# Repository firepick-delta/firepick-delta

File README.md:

### FirePick Delta Hardware/Mechanical Repo

#### Summary / Context

Design and Manufacturing Specifications for [FirePick Delta](http://delta.firepick.org).  If you're a developer wanting to help, the best way to do that is to join the [mailing list](https://groups.google.com/forum/#!forum/firepick) and start a line of communication there.  

This repo only contains the hardware (sch/pcb) and mechanical (3d) files for FirePick Delta.  It inherits software from OpenPnP, Marlin, and FirePick.  Other repo's of interest for FirePick Delta:

* https://github.com/firepick-delta/openpnp
* https://github.com/firepick-delta/Marlin
* https://github.com/firepick1/FireREST
* https://github.com/firepick1/FireBOM

#### Mechanical Assembly Parts Tree, Instructions, and BOM

Please click the link below to navigate the mechanical assembly with our FireBOM wiki documentation system:

[AFPD0001](AFPD0001) FirePick Delta Hacker-Developer Edition

#### Licensing

These files are licensed under [*Creative Commons Attribution-ShareAlike (CC BY-SA)*](https://creativecommons.org/licenses/by-sa/4.0/legalcode).  Commercial use is OK, but you are required under the license conditions to share your changes with the internet, and also credit the FirePick Delta team.

This license lets others remix, tweak, and build upon your work even for commercial purposes, as long as they credit you and license their new creations under the identical terms. This license is often compared to “copyleft” free and open source software licenses. All new works based on yours will carry the same license, so any derivatives will also allow commercial use. This is the license used by Wikipedia, and is recommended for materials that would benefit from incorporating content from Wikipedia and similarly licensed projects. 

[View License Deed](http://creativecommons.org/licenses/by-sa/4.0/) | [View Legal Code](https://creativecommons.org/licenses/by-sa/4.0/legalcode)

#### Contributors
* [@FlyingLotus1983 (Neil Jansen)](https://github.com/FlyingLotus1983)
* [@firepick1 (Karl Lew)](https://github.com/firepick1)
* [@ChristianLerche (Christian Lerche)](https://github.com/ChristianLerche)
* [@daytonpid (Dayton Pidhirney)](https://github.com/daytonpid)
* [@codedetail (Dave Shanklin)](https://github.com/codedetail)
* [@obnauticus (Thomas Kilbride)](https://github.com/obnauticus)
* [@mstegen (Mike Stegen)](https://github.com/mstegen)
* [@mikeanton (Mike Anton)](https://github.com/mikeanton)

#### Maintainers
* [@FlyingLotus1983 (Neil Jansen)](https://github.com/FlyingLotus1983)
* [@firepick1 (Karl Lew)](https://github.com/firepick1)

#### Contributions and Pull Requests

If you'd like to contribute anything back to this repo, please do so via [pull requests](https://help.github.com/articles/using-pull-requests).  

Keep in mind that the Cubify Design files are binary blobs.  Assembly (AD_ASM) files contain filepath links back to dependent solid parts (AD_PRT), and parts contain filepath links back to the assembly.  This makes it extremely tricky to use version control.  You can't just rename files all willy-nilly, or else Cubify will get very angry.  Please excercise caution and contact the FirePick Delta Dev Team via [google group mailing list](https://groups.google.com/forum/#!forum/firepick) before attempting to modify anything of significant nature.

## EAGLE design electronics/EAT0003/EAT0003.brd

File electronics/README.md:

### Electronic Design Directory

To add a new circuit design, first choose a new ID:

* **E** is the ID prefix for electronic parts (e.g., [ECAM01](../../../wiki/ECAM01)).

Archive your new design in git:

1. `git checkout dev`
1. Create a new directory (e.g., **ecam01**) and add your design files
1. `git add --all`
1. `git commit -am "adding new PCB"`
1. `git fetch; git merge; git push`

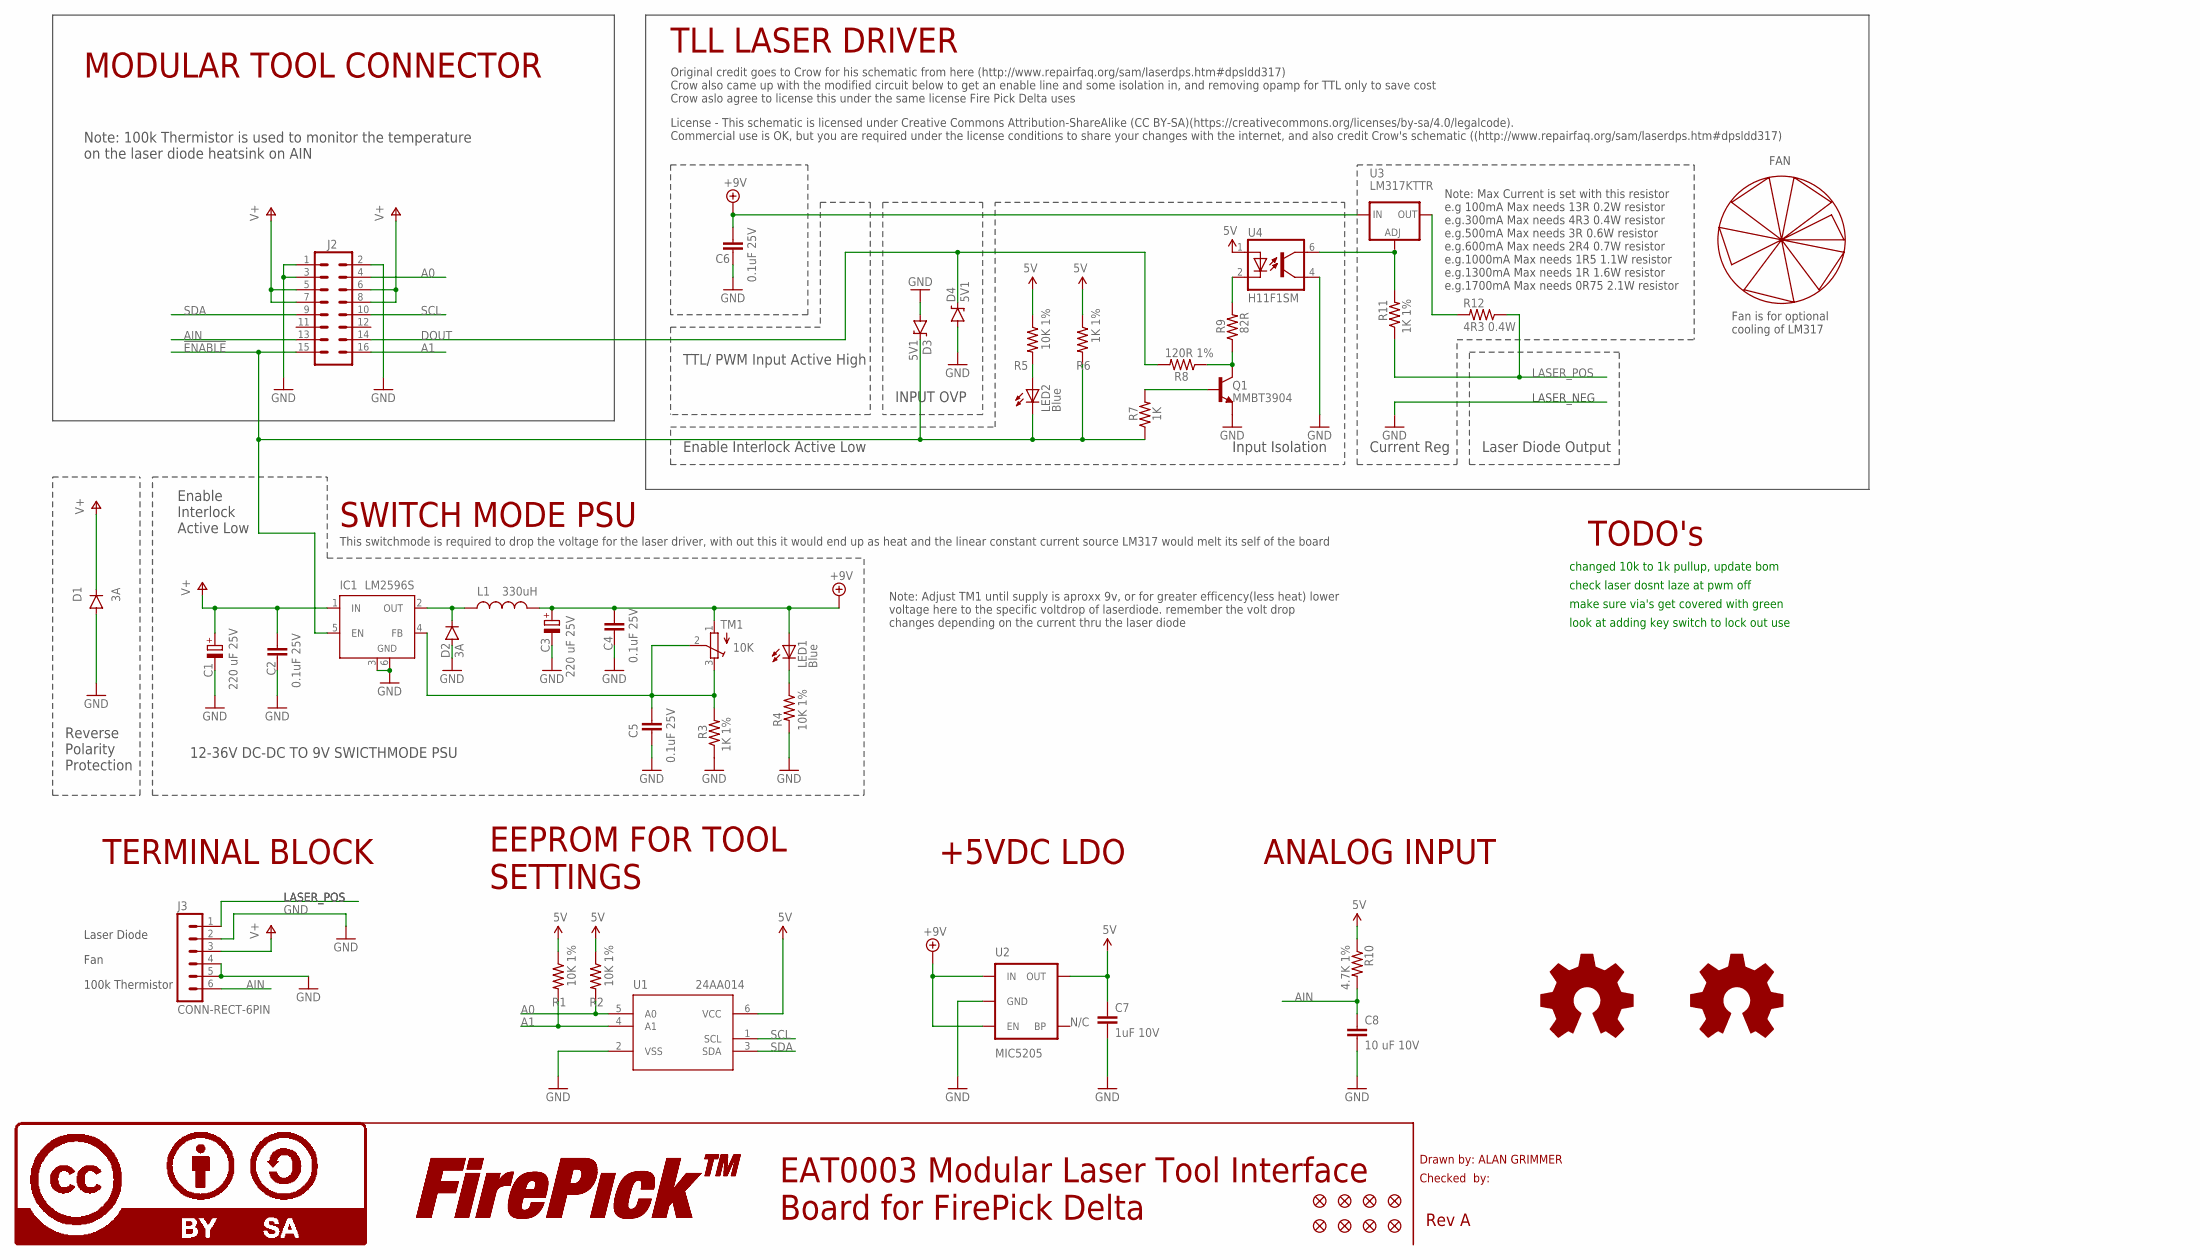
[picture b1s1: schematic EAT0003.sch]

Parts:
C1, C3: 220 uF 25V; UD-8X10_NICHICON
C2, C4, C5, C6: 0.1uF 25V; 0603-CAP
C7: 1uF 10V; 0603-CAP
C8: 10 uF 10V; 0805
D1, D2: 3A; SMA-DIODE
D3, D4: 5V1; SOD-323
FAN1: FAN_30MM; FAN_30MM_X_30MM
FID1, FID2, FID3, FID4, FID5, FID6, FID7, FID8: FIDUCIAL1X2; FIDUCIAL-1X2
IC1: LM2596S; TO263-5
J2: CONN-RECT-16PIN-2ROWSIDE; CONN-RECT-2.54MM-16PIN-2ROW-SIDE
J3: CONN-RECT-6PIN; CONN-OSTTE_6PIN
L1: 330uH; CDRH125
LED1, LED2: Blue; CHIPLED_0603
LOGO1, LOGO5: LOGO-CC-BY-SASMALL; LOGO-CC-BY-SA-SMALL
LOGO2, LOGO6: LOGO-FIREPICKSMALL; LOGO-FIREPICK-SMALL
LOGO3, LOGO4: LOGO-OSHWSMALL; LOGO-OSHW-SMALL
Q1: MMBT3904; SOT23-3
R1, R2, R4, R5: 10K 1%; 0603-RES
R3, R6, R11: 1K 1%; 0603-RES
R7: 1K; 0603-RES
R8: 120R 1%; 0603-RES
R9: 82R; 0603-RES
R10: 4.7K 1%; 0603-RES
R12: 4R3 0.4W; R2512
TM1: 10K; TC33X
U1: 24AA014; SOT23-6
U2: MIC5205; SOT23-5
U3: LM317KTTR; D2PAK-3
U4: H11F1SM; DIL6-SMD

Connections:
5V: C7.1, R1.1, R2.1, R5.1, R6.1, R10.1, U1.6 (VCC), U2.5 (OUT), U4.1 (A)
!ENABLE: D3.C, IC1.5 (EN), J2.15, LED2.C, R6.2, R7.1
+9V: C3.+, C4.1, C6.1, L1.2, LED1.A, TM1.1 (A), U2.1 (IN), U2.3 (EN), U3.3 (IN)
A0: J2.4, R2.2, U1.5 (A0)
A1: J2.16, R1.2, U1.4 (A1)
AIN: C8.1, J2.13, J3.6, R10.2
DOUT: D4.C, J2.14, R8.2
GND: C1.-, C2.2, C3.-, C4.2, C5.2, C6.2, C7.2, C8.2, D1.A, D2.A, D3.A, D4.A, IC1.3 (GND), IC1.6 (GND), J2.1, J2.2, J2.3, J3.2, J3.4, J3.5, Q1.2 (E), R3.1, R4.2, U1.2 (VSS), U2.2 (GND), U4.4 (EMIT)
LASER_POS: J3.1, R11.1, R12.1
unnamed: Q1.3 (C), R8.1, R9.1
unnamed: D2.C, IC1.2 (OUT), L1.1
unnamed: R11.2, U3.1 (ADJ), U4.6 (COL)
unnamed: R12.2, U3.2 (OUT), U3.PAD (OUT)
unnamed: LED1.C, R4.1
unnamed: R9.2, U4.2 (C)
unnamed: Q1.1 (B), R7.2
unnamed: LED2.A, R5.2
unnamed: C5.1, IC1.4 (FB), R3.2, TM1.2 (S), TM1.3 (E)
SCL: J2.10, U1.1 (SCL)
SDA: J2.9, U1.3 (SDA)
V+: C1.+, C2.1, D1.C, IC1.1 (IN), J2.5, J2.6, J2.7, J2.8, J3.3

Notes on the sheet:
Drawn by: ALAN GRIMMER
Checked by:
Rev A
EAT0003 Modular Laser Tool Interface Board for FirePick Delta
MODULAR TOOL CONNECTOR
EEPROM FOR TOOL SETTINGS
ANALOG INPUT
N/C
+5VDC LDO
TERMINAL BLOCK
TLL LASER DRIVER
Note: 100k Thermistor is used to monitor the temperature on the laser diode heatsink on AIN
Reverse Polarity Protection
12-36V DC-DC TO 9V SWICTHMODE PSU
changed 10k to 1k pullup, update bom
INPUT OVP
TTL/ PWM Input Active High
LASER_NEG
Enable Interlock Active Low
Input Isolation
Current Reg
Laser Diode Output
Enable Interlock Active Low
check laser dosnt laze at pwm off
SWITCH MODE PSU
Note: Adjust TM1 until supply is aproxx 9v, or for greater efficency(less heat) lower voltage here to the specific voltdrop of laserdiode. remember the volt drop changes depending on the current thru the laser diode
Note: Max Current is set with this resistor e.g 100mA Max needs 13R 0.2W resistor e.g.300mA Max needs 4R3 0.4W resistor e.g.500mA Max needs 3R 0.6W resistor e.g.600mA Max needs 2R4 0.7W resistor e.g.1000mA Max needs 1R5 1.1W resistor e.g.1300mA Max needs 1R 1.6W resistor e.g.1700mA Max needs 0R75 2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
Laser Diode
Fan
100k Thermistor
Original credit goes to Crow for his schematic from here (http://www.repairfaq.org/sam/laserdps.htm#dpsldd317) Crow also came up with the modified circuit below to get an enable line and some isolation in, and removing opamp for TTL only to save cost Crow aslo agree to license this under the same l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
FAN
make sure via's get covered with green
License - This schematic is licensed under Creative Commons Attribution-ShareAlike (CC BY-SA)(https://creativecommons.org/licenses/by-sa/4.0/legalcode). Commercial use is OK, but you are required under the license conditions to share your changes with the internet, and also credit Crow's schematic 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
This switchmode is required to drop the voltage for the laser driver, with out this it would end up as heat and the linear constant current source LM317 would melt its self of the board
Fan is for optional cooling of LM317
TODO's
look at adding key switch to lock out use

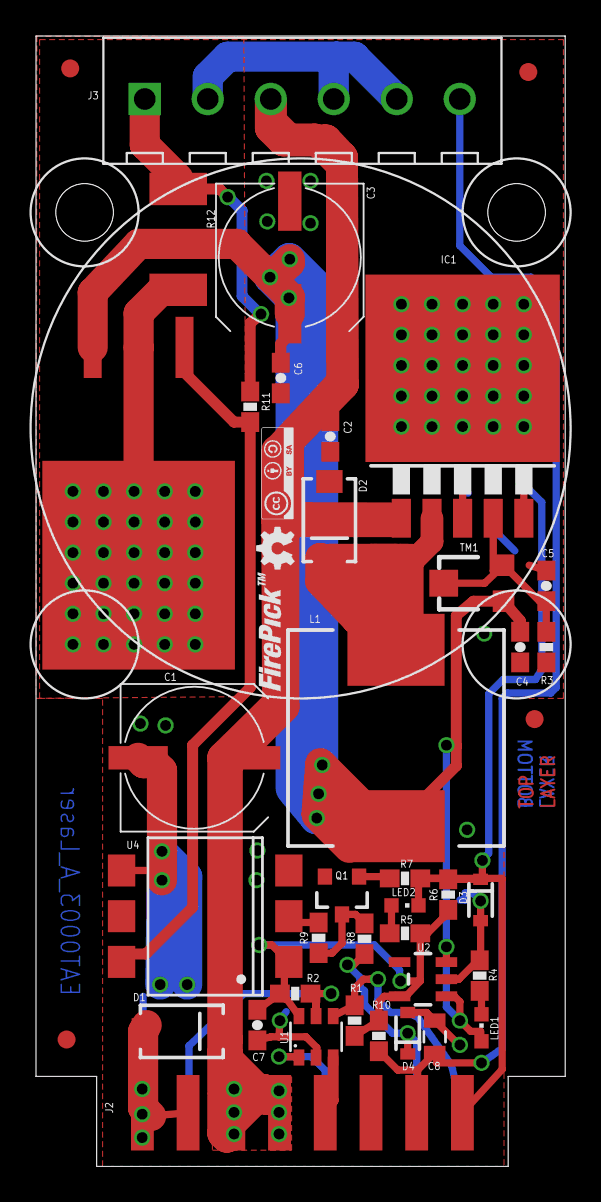
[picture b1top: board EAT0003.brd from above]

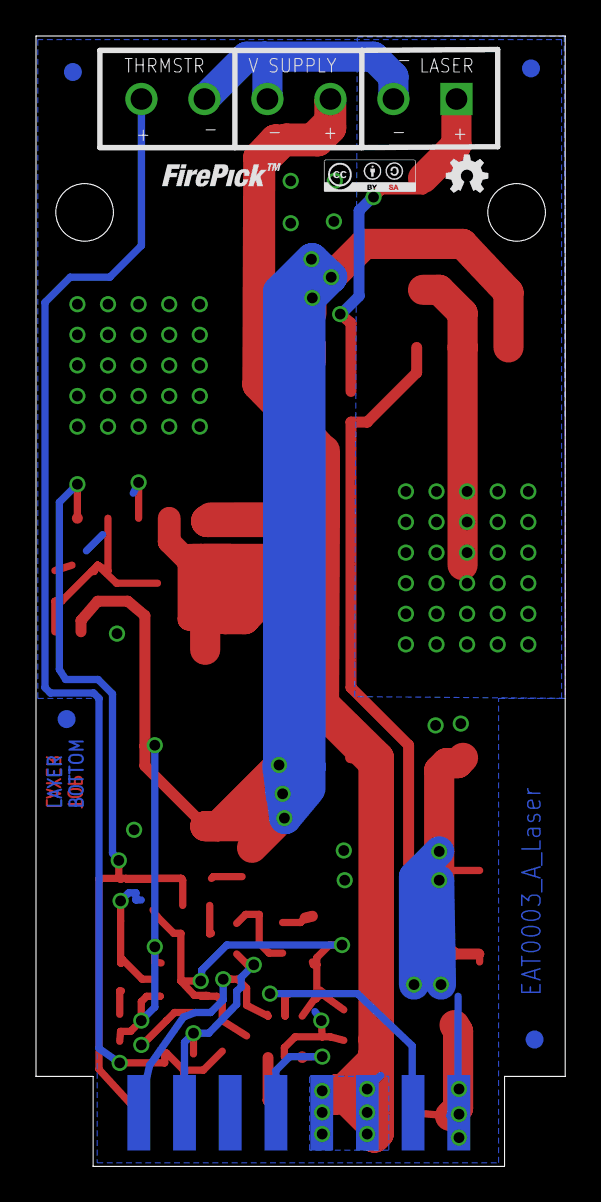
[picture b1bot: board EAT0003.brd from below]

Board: 2 copper layers, 29.4 x 62.8 mm, 51 parts (7 on the bottom side), 21 nets.

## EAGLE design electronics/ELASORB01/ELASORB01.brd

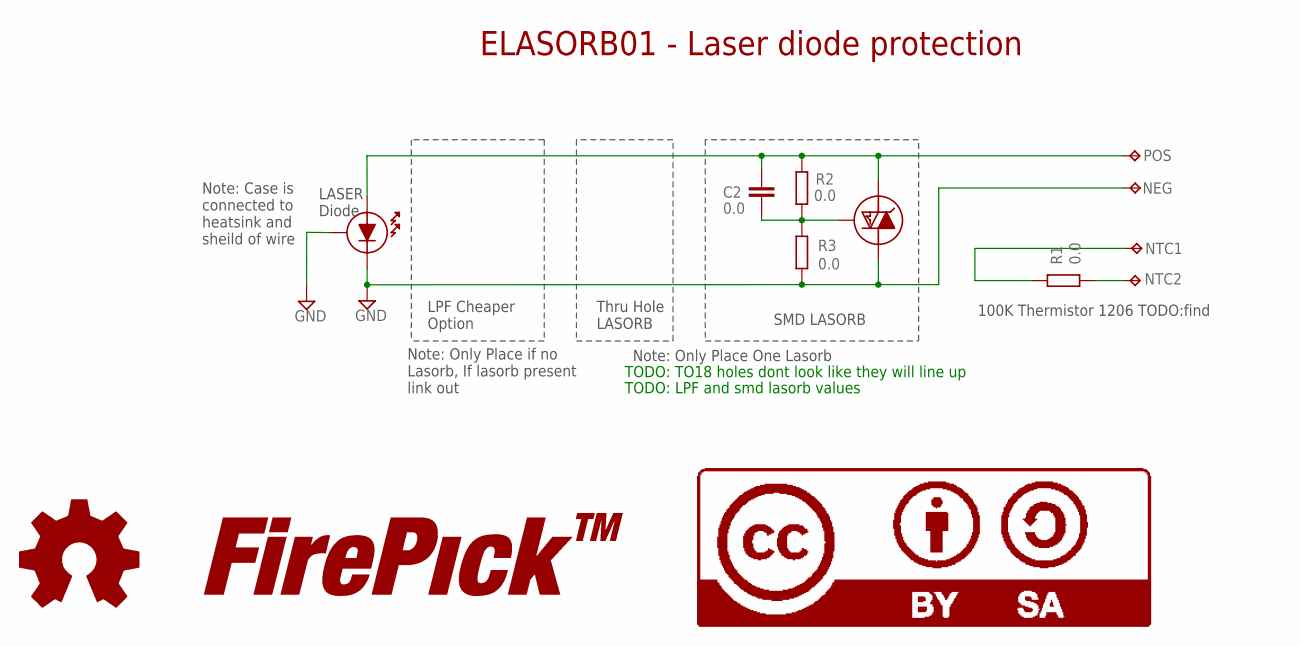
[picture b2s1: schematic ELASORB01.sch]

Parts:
C2: 0.0; C0603K
D1: LASER_DIODE; TO18
LOGO1: LOGO-CC-BY-SASMALL; LOGO-CC-BY-SA-SMALL
LOGO2: LOGO-FIREPICKSMALL; LOGO-FIREPICK-SMALL
LOGO3: LOGO-OSHWSMALL; LOGO-OSHW-SMALL
NEG: TPTP16R; TP16R
NTC1, NTC2: TPTP16R; TP16R
POS: TPTP16R; TP16R
R1: 0.0; R1206
R2, R3: 0.0; R0603
U2: LASORB_SMD; TSOP-6

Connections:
GND: D1.2 (CASE), D1.3 (K), NEG.TP, R3.2, U2.P$4 (LDK)
unnamed: NTC2.TP, R1.2
unnamed: NTC1.TP, R1.1
unnamed: C2.1, D1.1 (A), POS.TP, R2.2, U2.P$1 (LDA), U2.P$2 (LDA), U2.P$5 (LDA), U2.P$6 (LDA)
unnamed: C2.2, R2.1, R3.1, U2.P$3 (3-TRIG)

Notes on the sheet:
Thru Hole LASORB
SMD LASORB
Note: Case is connected to heatsink and sheild of wire
Note: Only Place One Lasorb
LASER Diode
TODO: TO18 holes dont look like they will line up
LPF Cheaper Option
TODO: LPF and smd lasorb values
Note: Only Place if no Lasorb, If lasorb present link out
ELASORB01 - Laser diode protection
100K Thermistor 1206 TODO:find

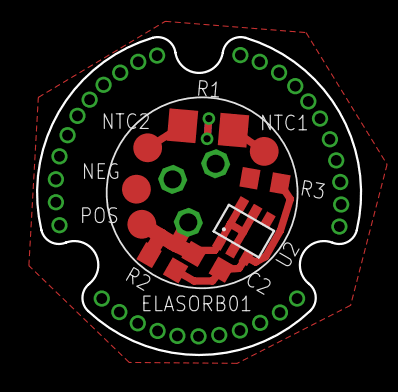
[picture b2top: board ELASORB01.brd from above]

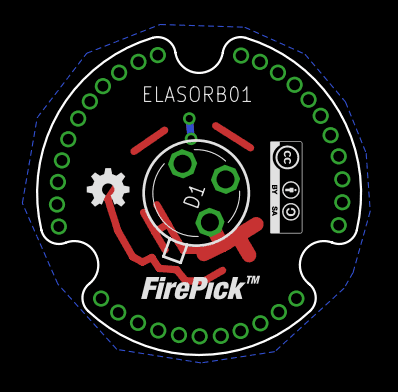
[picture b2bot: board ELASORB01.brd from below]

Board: 2 copper layers, 18.0 x 17.7 mm, 13 parts (4 on the bottom side), 5 nets.

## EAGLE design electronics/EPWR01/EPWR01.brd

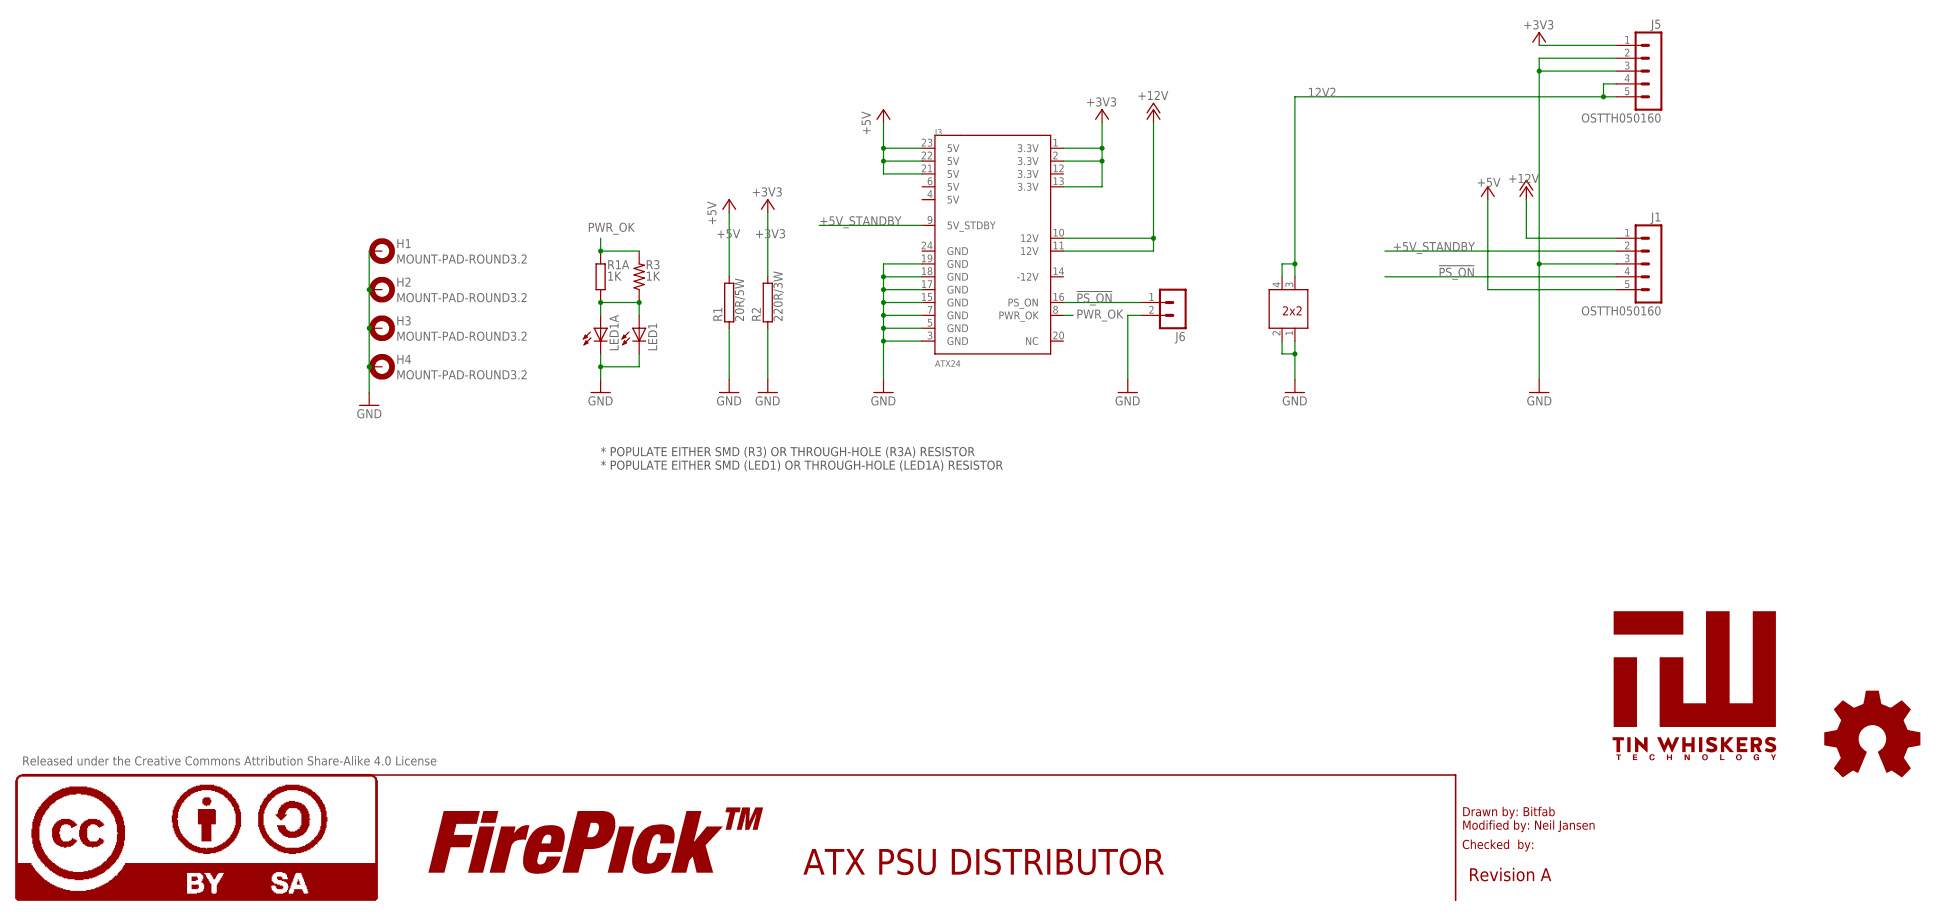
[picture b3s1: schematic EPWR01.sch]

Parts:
H1, H2, H3, H4: MOUNT-PAD-ROUND3.2; 3,2-PAD
J1, J5: OSTTH050160; CONN-OSTTH050160; PARTNO OSTTH050160
J3: ATX24; PARTNO 2-1586043-4
J4: ATX2X2; PARTNO 1586041-4
J6: MA02-1; PARTNO CONN-0.1-RA-1X2
LED1: LED1206; LED-1206; PARTNO LTST-C150AKT
LED1A: LED3MM; PARTNO *
LOGO4: LOGO-FIREPICKLARGE; LOGO-FIREPICK
LOGO5: LOGO-OSHWMEDIUM; LOGO-OSHW-MEDIUM
LOGO6: LOGO-CC-BY-SALARGE; LOGO-CC-BY-SA
R1: 20R/5W; HPS923; PARTNO SQP500JB-20R
R1A: 1K; 0207/10
R2: 220R/3W; CA4050; PARTNO PNP3WVJR-73-220R
R3: 1K; 0805; PARTNO RC0805FR-071KL
U$1: TIN-WHISKERSSMALL; TIN-WHISKERS-SMALL

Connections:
12V2: J4.3, J4.4, J5.4, J5.5
!PS_ON: J1.4, J3.16 (PS_ON), J6.1
+3V3: J3.1 (3.3V), J3.2 (3.3V), J3.13 (3.3V), J5.1, R2.2
+5V: J1.5, J3.21 (5V), J3.22 (5V), J3.23 (5V), R1.2
+5V_STANDBY: J1.2, J3.9 (5V_STDBY)
+12V: J1.1, J3.10 (12V), J3.11 (12V)
GND: H1.B3,2, H2.B3,2, H3.B3,2, H4.B3,2, J1.3, J3.3 (GND), J3.5 (GND), J3.7 (GND), J3.15 (GND), J3.17 (GND), J3.18 (GND), J3.19 (GND), J4.1, J4.2, J5.2, J5.3, J6.2, LED1.C, LED1A.K (C), R1.1, R2.1
unnamed: LED1.A, LED1A.A, R1A.1, R3.1
PWR_OK: J3.8 (PWR_OK), R1A.2, R3.2

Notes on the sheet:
Drawn by: Bitfab Modified by: Neil Jansen
Checked by:
Revision A
ATX PSU DISTRIBUTOR
Released under the Creative Commons Attribution Share-Alike 4.0 License
* POPULATE EITHER SMD (R3) OR THROUGH-HOLE (R3A) RESISTOR * POPULATE EITHER SMD (LED1) OR THROUGH-HOLE (LED1A) RESISTOR

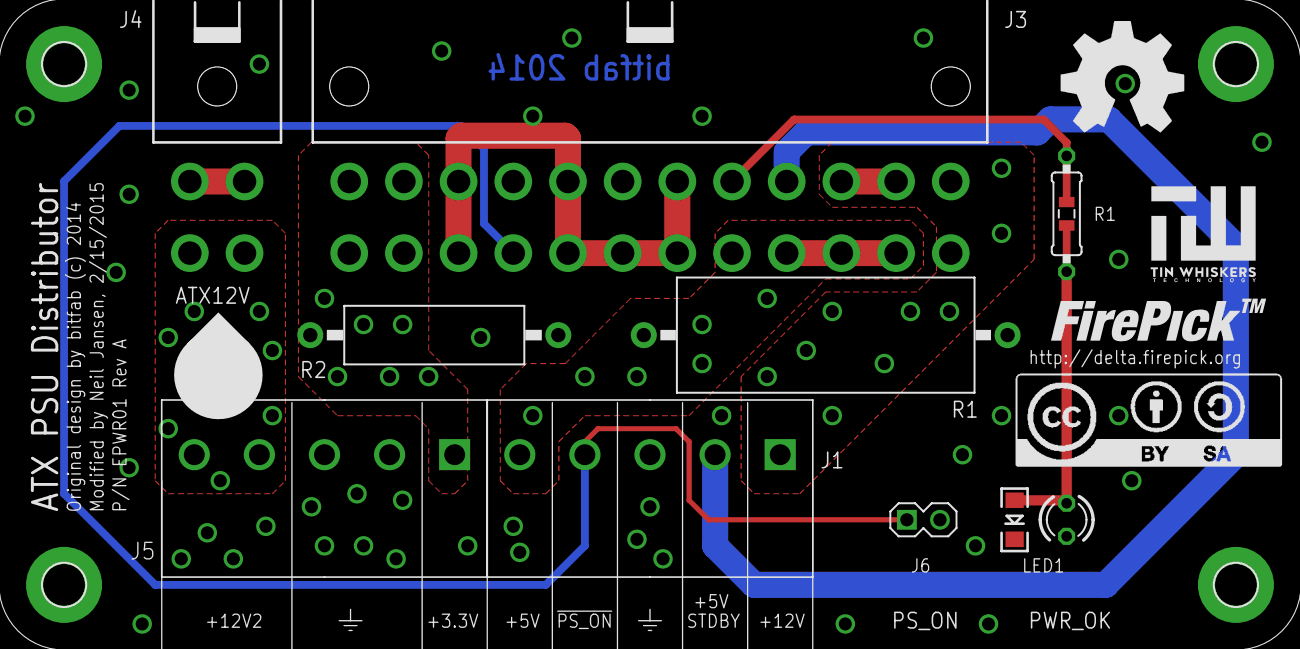
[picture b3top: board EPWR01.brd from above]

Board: 2 copper layers, 21 parts (0 on the bottom side), 9 nets.

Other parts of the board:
U$5: REPRAP_BSTOP
U$6: OSHS_10X200_BSTOP

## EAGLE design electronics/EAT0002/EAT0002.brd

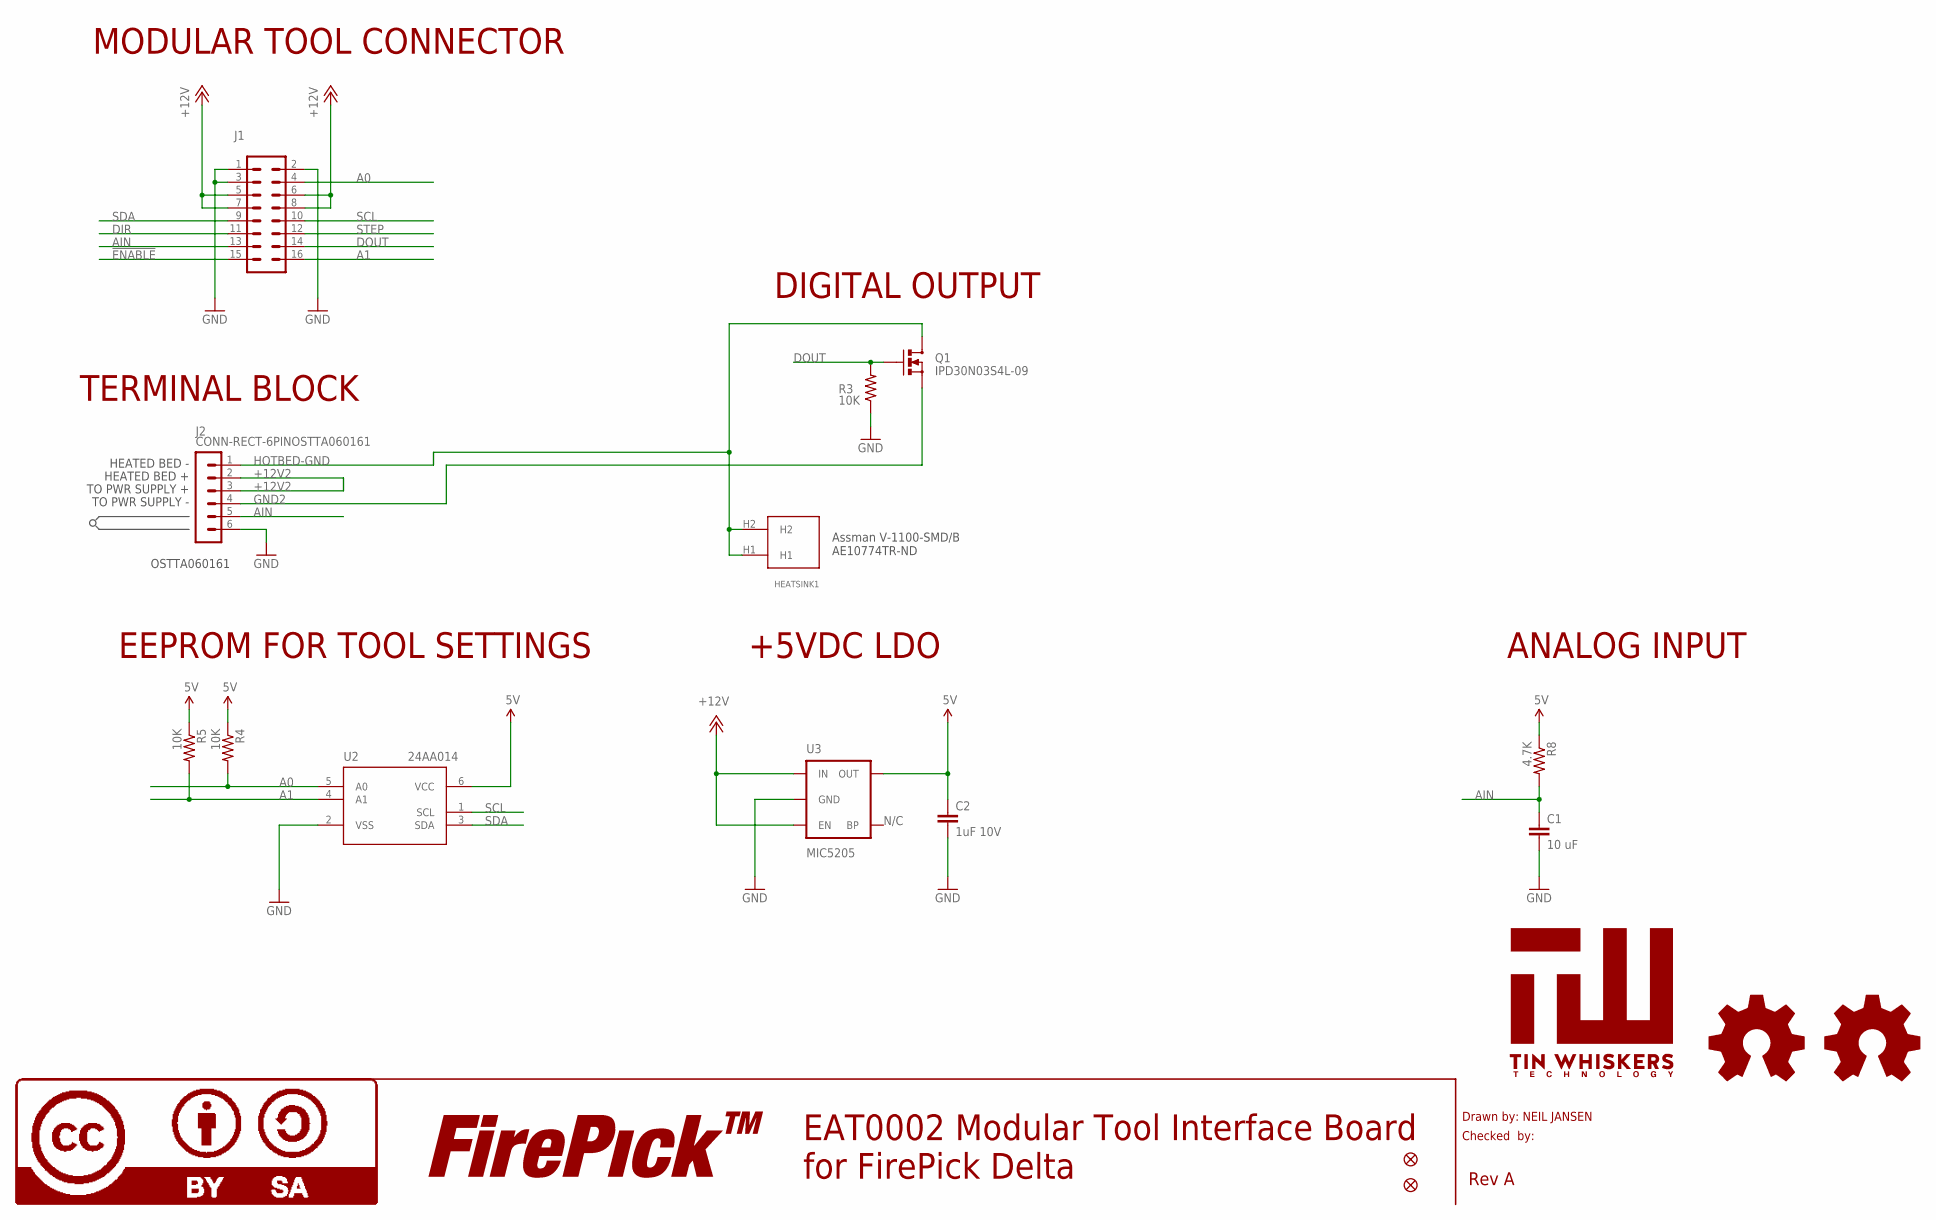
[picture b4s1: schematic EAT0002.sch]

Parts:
C1: 10 uF; 0805; PARTNO CC0805ZKY5V6BB106
C2: 1uF 10V; 0805; PARTNO CC0805KKX7R7BB105
FID1, FID2: FIDUCIAL
HEATSINK1: HEATSINK-DPAK; PARTNO V-1100-SMD/B
J1: CONN-RECT-16PIN-2ROWSIDE; CONN-RECT-2.54MM-16PIN-2ROW-SIDE; PARTNO CONN-0.1-S-2x8
J2: CONN-RECT-6PINOSTTA060161; CONN-OSTTA060161; PARTNO OSTTA060161
LOGO1, LOGO5: LOGO-OSHWSMALL; LOGO-OSHW-SMALL
LOGO4: LOGO-FIREPICKMEDIUM; LOGO-FIREPICK-MEDIUM
LOGO6: LOGO-CC-BY-SAMEDIUM; LOGO-CC-BY-SA-MEDIUM
Q1: IPD30N03S4L-09; DPAK; PARTNO IPD30N03S4L-09
R3, R4, R5: 10K; 0805; PARTNO RC0805FR-0710KL
R8: 4.7K; 0805; PARTNO RC0805FR-074K7L
U2: 24AA014; SOT23-6; PARTNO 24AA014T-I/OT
U3: MIC5205; SOT23-5; PARTNO MIC5205-5.0YM5 TR
U$1: TIN-WHISKERSSMALL; TIN-WHISKERS-SMALL

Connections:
5V: C2.1, R4.1, R5.1, R8.1, U2.6 (VCC), U3.5 (OUT)
!ENABLE: J1.15
+12V: J1.5, J1.6, J1.7, J1.8, U3.1 (IN), U3.3 (EN)
+12V2: J2.2, J2.3
A0: J1.4, R4.2, U2.5 (A0)
A1: J1.16, R5.2, U2.4 (A1)
AIN: C1.1, J1.13, J2.5, R8.2
DIR: J1.11
DOUT: J1.14, Q1.1 (G), R3.2
GND: C1.2, C2.2, J1.1, J1.2, J1.3, J2.6, R3.1, U2.2 (VSS), U3.2 (GND)
GND2: J2.4, Q1.3 (S)
HOTBED-GND: HEATSINK1.H1, HEATSINK1.H2, J2.1, Q1.4 (D)
SCL: J1.10, U2.1 (SCL)
SDA: J1.9, U2.3 (SDA)
STEP: J1.12

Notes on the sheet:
Drawn by: NEIL JANSEN
Checked by:
Rev A
EAT0002 Modular Tool Interface Board for FirePick Delta
MODULAR TOOL CONNECTOR
DIGITAL OUTPUT
EEPROM FOR TOOL SETTINGS
ANALOG INPUT
N/C
+5VDC LDO
TERMINAL BLOCK
OSTTA060161
Assman V-1100-SMD/B AE10774TR-ND
TO PWR SUPPLY -
TO PWR SUPPLY +
HEATED BED +
HEATED BED -

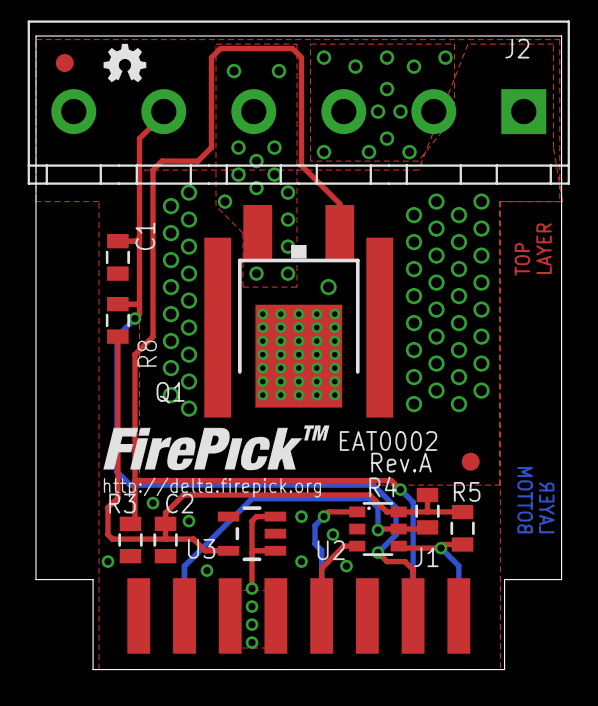
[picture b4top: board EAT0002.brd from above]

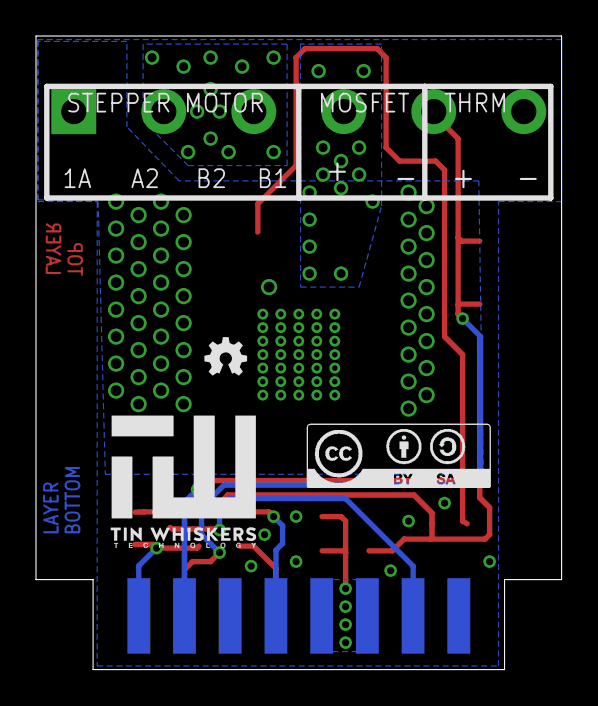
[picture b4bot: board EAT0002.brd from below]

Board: 2 copper layers, 29.2 x 35.2 mm, 19 parts (3 on the bottom side), 12 nets.

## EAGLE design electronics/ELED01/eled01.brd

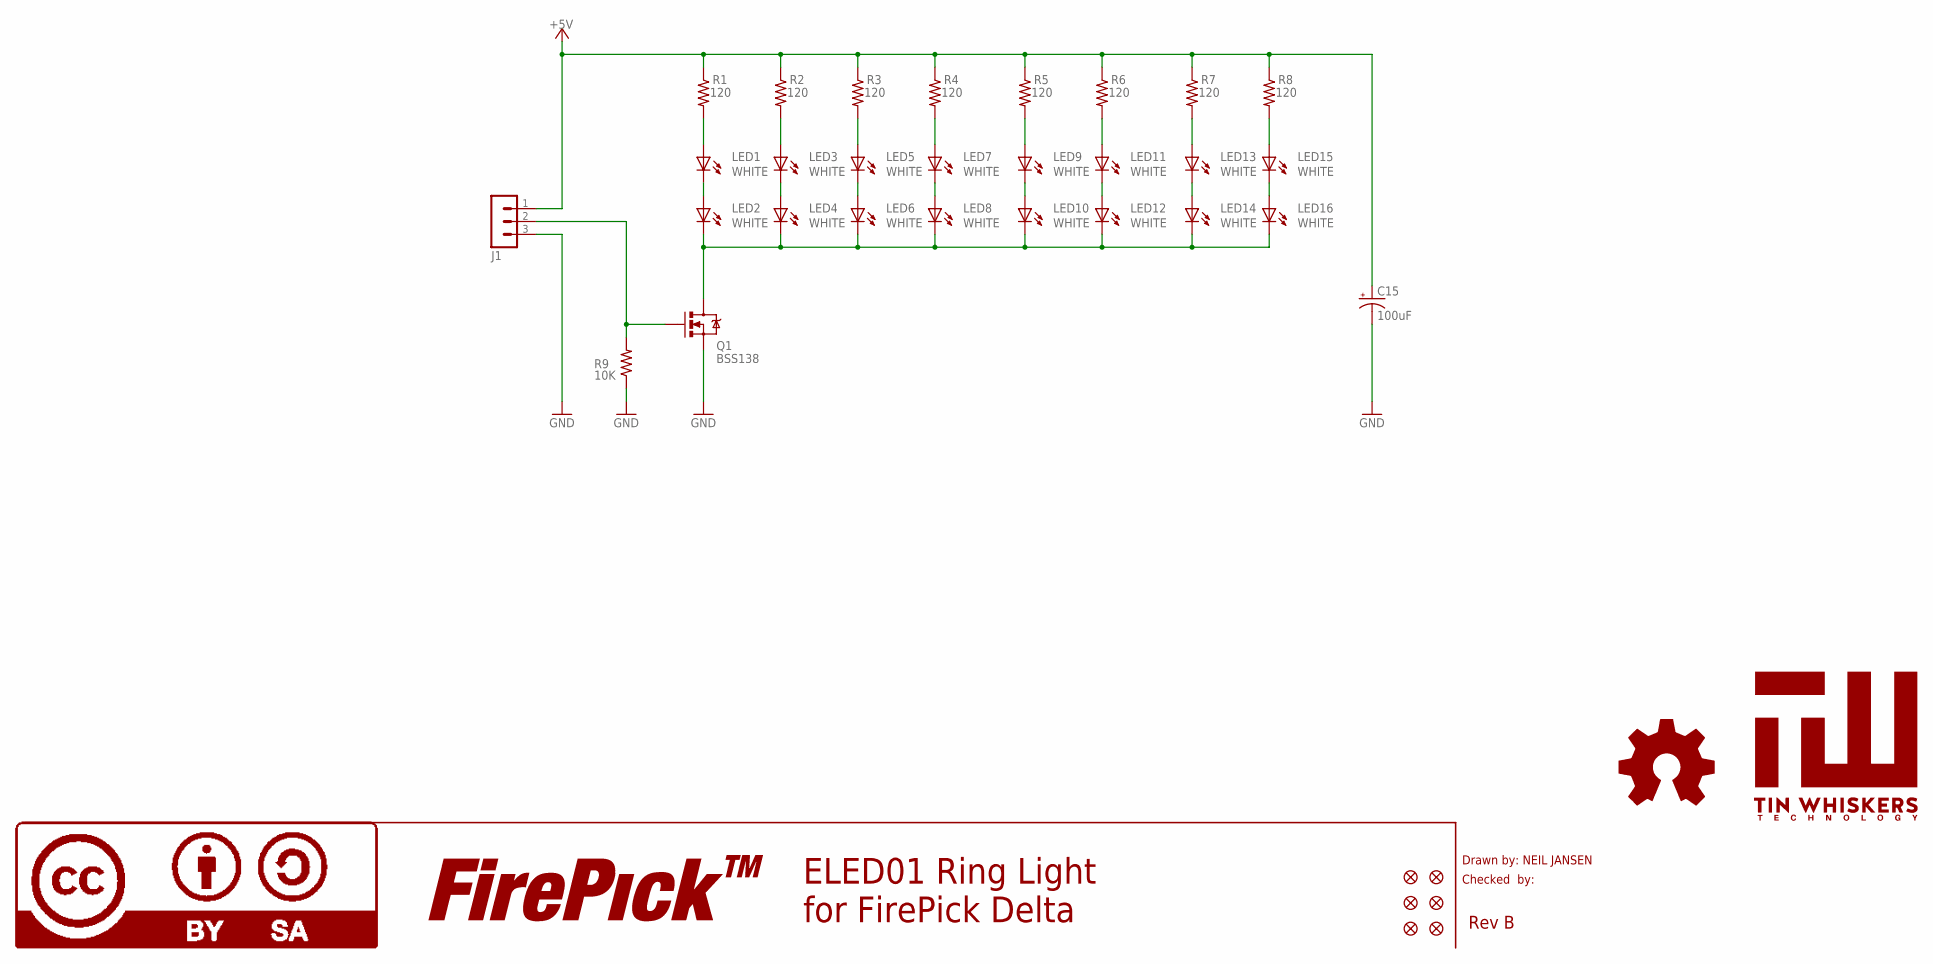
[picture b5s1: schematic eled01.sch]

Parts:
C15: 100uF; PANASONIC_D; PARTNO 25TXV100M6.3X8
FID1, FID2, FID3, FID4, FID5, FID6: FIDUCIAL
J1: MA03-1; PARTNO CONN-0.1-RA-1X3
LED1, LED2, LED3, LED4, LED5, LED6, LED7, LED8, LED9, LED10, LED11, LED12, LED13, LED14, LED15, LED16: WHITE; LED-1206-NO_SILK; PARTNO LTST-C150CKT
LOGO2: LOGO-OSHWSMALL; LOGO-OSHW-SMALL
LOGO4: LOGO-FIREPICKMEDIUM; LOGO-FIREPICK-MEDIUM
LOGO6: LOGO-CC-BY-SAMEDIUM; LOGO-CC-BY-SA-MEDIUM
Q1: BSS138; SOT23; PARTNO BSS138
R1, R2, R3, R4, R5, R6, R7, R8: 120; 0805; PARTNO RC0805FR-07120RL
R9: 10K; 0805; PARTNO RC0805FR-0710KL
U$1: TIN-WHISKERSSMALL; TIN-WHISKERS-SMALL

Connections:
+5V: C15.+, J1.1, R1.1, R2.1, R3.1, R4.1, R5.1, R6.1, R7.1, R8.1
DRAIN: LED2.C, LED4.C, LED6.C, LED8.C, LED10.C, LED12.C, LED14.C, LED16.C, Q1.3 (D)
ENABLE1: J1.2, Q1.1 (G), R9.2
GND: C15.-, J1.3, Q1.2 (S), R9.1
unnamed: LED1.C, LED2.A
unnamed: LED3.C, LED4.A
unnamed: LED7.C, LED8.A
unnamed: LED7.A, R4.2
unnamed: LED3.A, R2.2
unnamed: LED5.A, R3.2
unnamed: LED9.A, R5.2
unnamed: LED11.A, R6.2
unnamed: LED9.C, LED10.A
unnamed: LED5.C, LED6.A
unnamed: LED11.C, LED12.A
unnamed: LED13.C, LED14.A
unnamed: LED15.C, LED16.A
unnamed: LED13.A, R7.2
unnamed: LED15.A, R8.2
unnamed: LED1.A, R1.2

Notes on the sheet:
Drawn by: NEIL JANSEN
Checked by:
Rev B
ELED01 Ring Light for FirePick Delta

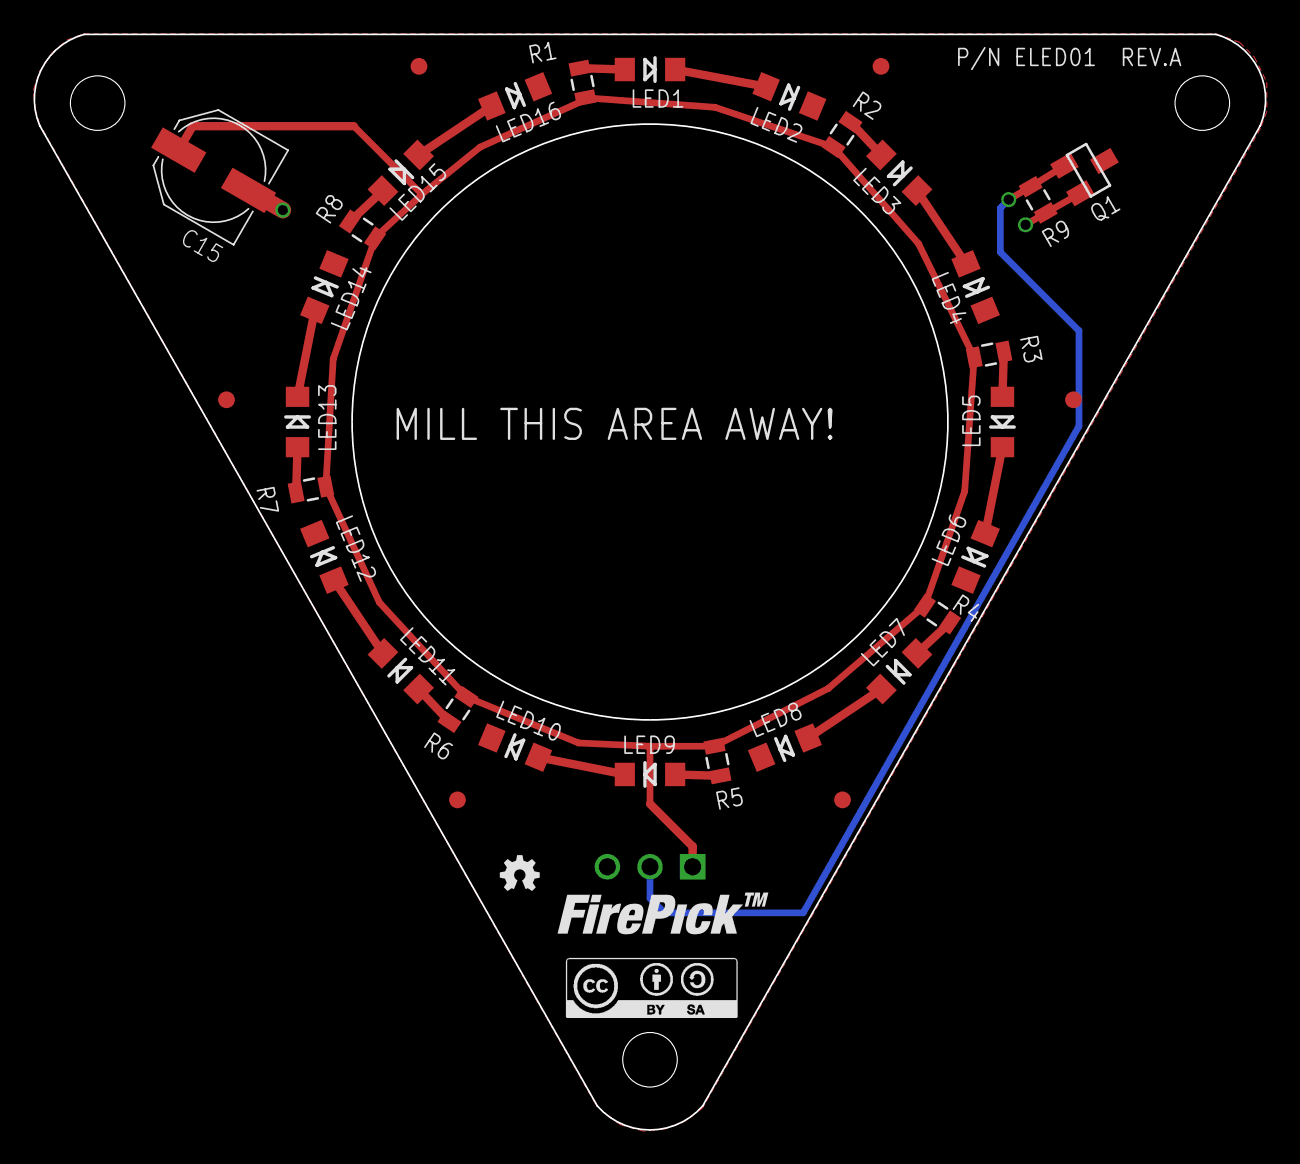
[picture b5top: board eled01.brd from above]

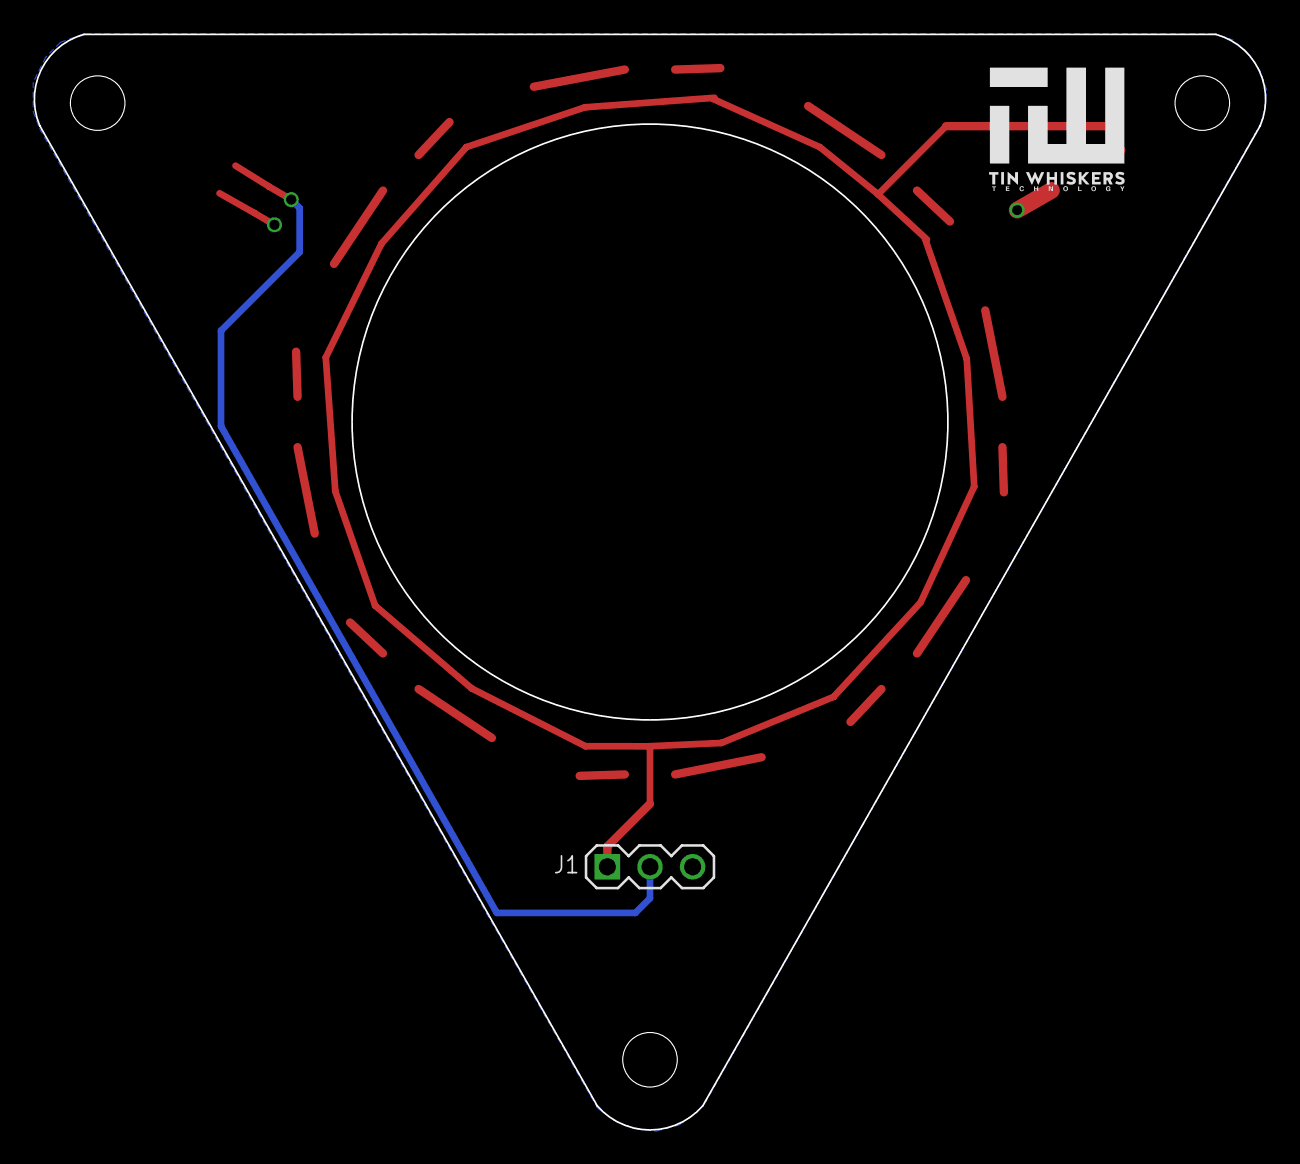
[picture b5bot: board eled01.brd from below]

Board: 2 copper layers, 73.4 x 65.3 mm, 38 parts (2 on the bottom side), 20 nets.

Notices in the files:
electronics/EAT0003/EAT0003.sch:
Crow aslo agree to license this under the same license Fire Pick Delta uses
Commercial use is OK, but you are required under the license conditions to share your changes with the internet, and also credit Crow's schematic ((http://www.repairfaq.org/sam/laserdps.htm#dpsldd317)
electronics/EPWR01/EPWR01.brd:
Original design by bitfab (c) 2014
electronics/emc01/FPC-EMC01-1284.brd:
CC-BY-SA 4.0 license
parts and their libraries:
SparkFun-Capacitors: Licensing: Creative Commons ShareAlike 4.0 International - https://creativecommons.org/licenses/by-sa/4.0
